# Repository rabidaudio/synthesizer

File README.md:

# Synth

> These are my custom modules for a from-scratch [Eurorack](https://en.wikipedia.org/wiki/Eurorack) analog synthesizer.

https://rabid.audio/projects/synth

## Modules

1. [Amplifier](amp)
  - LM13700
  - matched-pair PNP exponential converter
  - CV of 10V -> Gain=1
  - CV of <=0V -> Gain=\~0, 6 decades below Gain=1
  - allow overdrive to Gain=2
    - ideally this would begin to clip
  - mixdown
    - mono - full mix -> left and right
    - stereo split - A+C->left B+D->right
  - Direct stereo input jack
    - mix arbitrary signal with mixdown
    - e.g. for accepting signals from other synths
2. [Oscillator](vco)
  - 0-10V, 1V/octave, A0 to A10
  - Square/Triangle core via LM13700
  - Waveshapper for triangle -> sine
  - PWM control
    - triangle wave applied to comparator with CV controlling reference. Triangle wave means CV is linear
  - abs(triangle) can be used for 2x square
    - adds a lot of parts for little benefit
  - blending shapes isn't useful here, since we could use other oscillators for that
  - Option to sync with another osc?
    - in theory, grounding osc at a regular interval would reset the osc over and over, effectively changing it's frequency
  - CV control for shape?
  - Room for more shapes
    - white noise?
    - PDS
      - https://en.wikipedia.org/wiki/Phase_distortion_synthesis
      - a bit of wild harmonics
      - multiplication techniques
        - log/antilog
        - https://en.wikipedia.org/wiki/Gilbert_cell
        - AD633 ($11-$13 /unit on DigiKey!?)
        - EL4450C ($4/unit on Digikey but out of stock). It's a little more awkward to use since it's max differerential input voltage for linearity is 2V
      - the hard part will be the "slightly higher frequency" bit
        - perhaps instead you have another osc (555?) running at a fixed frequency and clipping the sine
        - square PWM control could also adjust this clip frequency
      - In Max you do PDS by `kink~`-ing a `phasor~` and using that to drive the phase of `cycle~`. Kink is somewhat straightforward to do - use a comparator to adjust the charge current after a threshold. But how you drive a sine wave phase with that I'm not sure
    - down ramp wave with just a JFET
      - up ramp wave probably needs another JFET and an inverter
    - sub octave
      - theory and example circuit: http://www.valvewizard.co.uk/uboat.html
    - octave
      - full wave rectifier
    - multiplying the triangle with a square wave with different phases and pulse-widths gives some neat sounds
    - polynomial
      - The EL4450C datasheet describes using a multiplier ic to create a polynomial of the form (k1 v^2 + v) / k2
      - it sounds like crap on a triangle wave and does nothing for a square wave, but it adds a nice second harmonic to a sine wave
      - from experiments in Max, good values are k1=1.5-2.5, k2=2
      - but at that point, should you just use 2 oscillators?
3. [A/D/S/R envelope](adsr)
  - 4 envelopes required for 4-voice polyphony
  - wired to VCA by default
  - save surface area with 1 set of ADSR controls for a pair of envelopes
  - fully modular means you could borrow one for VCF instead, or send to both VCA and VCF
4. Filter
  -  4P LP(/HP?)
  - Cutoff frequency control has same range as oscillator
    - 0-10V, 1V/octave, A0 to A10
  - filter we designed for class
    - standard vactrols are available on Thonk
  - CV control of cutoff + resonance
  - Default to track cutoff with VCO-CV
  - individual filter knobs, plus a global knob for filter sweeps
5. [Utilities](utils)
  - Buffer, Sum, Attenuate, Invert, Gate
  - Could be all-in one
    - A input (default ground)
    - B input (default ground)
    - level knob attenuator
    - gate digital CV in, default on
    - `(A+B)*level*gate` output
    - `-(A+B)*level*gate` output
    - Constant CV out if A and B disconnected

Bitcrusher?
4 filters or one?
Noise?
Clock?
Headphone output no longer required
2D mixer?

## TODO

- utility module
  - [x] Verify on breadboard
  - [x] design PCB
  - [x] order parts
  - [x] come up with a cute name
  - [x] design front panel
  - [x] assemble Rev. A PCB
    - bend the regulators first
    - plenty of 4066s
    - flip orientation of power connector
    - pot orientation - both channels:
      - right side (facing) to inside of board (from top)
      - left side (facing) to outside of board (from top)
  - [x] test with Neutron
    - constant output is only 9 to -7.8
    - high noise when used as a buffer
      - perhaps input signal is clipping?
      - white noise when the gain is turned down
  - [x] adjust design for Rev. B
  - [x] assemble Rev. B proto board
  - fix prototype issues
    - [ ] sum pot is backwards
    - [ ] a bit of noise on the constant output near the center
    - [ ] verify output levels
    - [ ] hard click on gate
      - needs a LPF?
  - [ ] assemble Rev. B PCB
  - [ ] manufacture front panel
  - [ ] assemble module
- VCA
  - [x] Confirm amp on breadboard, finalize CV levels
  - [x] figure out where tuning trimmers are needed
  - [x] build prototype
  - fix prototype issues
    - [ ] output is too quiet for headphones, need about 2x gain
    - [ ] CV range is too wide, adjust scaling for faster change in db/V
  - [ ] finish PCB schematic for complete amplifier
  - [ ] Create PCB
  - [ ] design front panel
  - [ ] manufacture front panel
  - [ ] assemble module
- VCO
  - [ ] design core
    - [x] core osc - square/triangle
    - [x] wave shaper (sine)
    - [x] pwm control
    - [ ] additional shape
    - [x] shape selection
  - [x] Confirm amp on breadboard, finalize CV levels
  - fix breadboard test issues
    - [ ] pitch is very sensitive to power supply noise
    - [ ] tuning is rather difficult
  - [ ] Build prototype
  - fix prototype issues
    - TBD
  - [ ] design PCB
  - [ ] Create PCB
  - [ ] design front panel
  - [ ] manufacture front panel
  - [ ] assemble module
- Envelope
  - [x] design in SPICE
  - [ ] verify on breadboard
  - [ ] build prototype
  - fix prototype issues
    - TBD
  - [ ] design PCB
  - [ ] Create PCB
  - [ ] design front panel
  - [ ] manufacture front panel
  - [ ] assemble module
- VCF
  - TBD
- build tools
  - [x] tiny Breakout pcbs for headphone jacks
  - ~~transistor matcher circuit~~
    - bought matched pair BJTs instead
  - [x] quantized selector with hysteresis

## License

Schematics, board layouts, documentation, etc. is licensed under [Creative Commons Attribution-NonCommercial-ShareAlike 4.0 International License](http://creativecommons.org/licenses/by-nc-sa/4.0/).

If you're interested in commercial use, please ask first.

Any source code is licensed under [MIT](SOFTWARE_LICENSE).

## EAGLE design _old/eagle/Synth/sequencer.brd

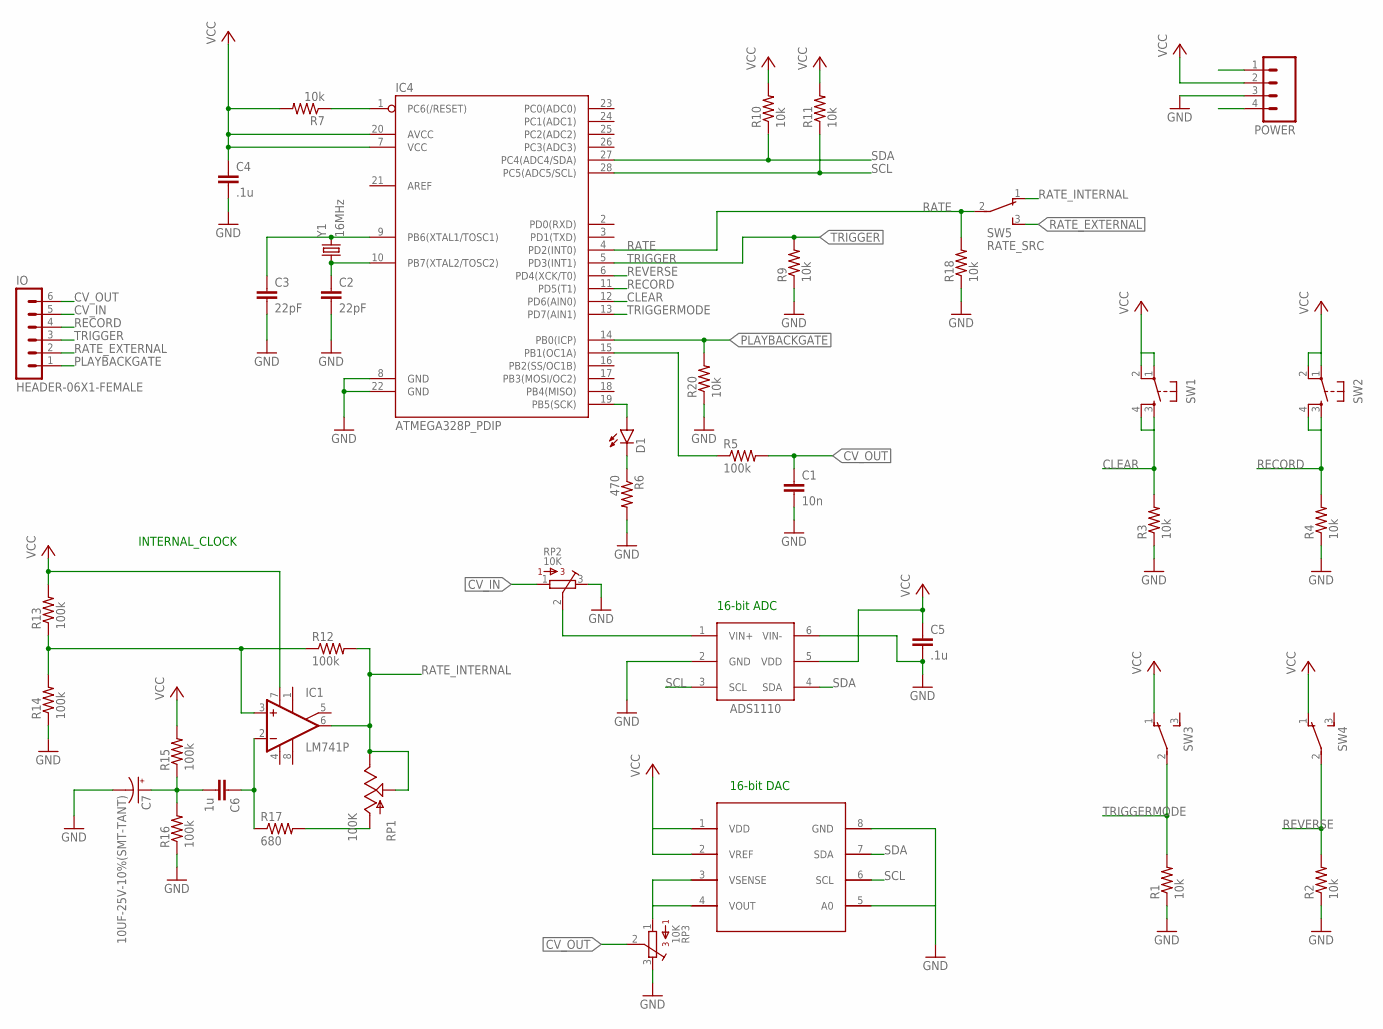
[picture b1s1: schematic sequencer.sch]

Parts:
C1: 10n; 1206
C2, C3: 22pF; 1206
C4, C5: .1u; 1206
C6: 1u; 1206
C7: 10UF-25V-10%(SMT-TANT); EIA6032-NOM
D1: LED-3MM-NO_SILK; LED3MM-NS
IC1: LM741P; DIL08
IC2: ADS1110; SOT-23-6
IC3: DAC8571; 8MSOP
IC4: ATMEGA328P_PDIP; DIL28-3
IO: HEADER-06X1-FEMALE; 06X1-PTH
POWER: M04PTH; 1X04
R1, R2, R3, R4, R7, R9, R10, R11, R18, R20: 10k; 1206
R5, R12, R13, R14, R15, R16: 100k; 1206
R6: 470; 1206
R17: 680; 1206
RP1: 100K; ALPS_POT_KIT
RP2, RP3: 10K; 3386P
SW1, SW2: TAC_SWITCHPTH; TACTILE-PTH
SW3, SW4: TL36YO; TL3XYO
SW5: RATE_SRC; TL3XYO
Y1: 16MHz; HC49US

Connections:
CLEAR: IC4.12 (PD6(AIN0)), R3.2, SW1.3, SW1.4
CV_IN: IO.5, RP2.1
CV_OUT: C1.1, IO.6, R5.2, RP3.2
DIRECT_IN: IC2.1 (VIN+), RP2.2
GND: C1.2, C2.2, C3.2, C4.2, C5.2, C7.C (-), IC2.2 (GND), IC2.6 (VIN-), IC3.5 (A0), IC3.8 (GND), IC4.8 (GND), IC4.22 (GND), POWER.3, R1.1, R2.1, R3.1, R4.1, R6.2, R9.1, R14.1, R16.1, R18.1, R20.1, RP2.3, RP3.3
unnamed: IC4.15 (PB1(OC1A)), R5.1
unnamed: IC3.3 (VSENSE), IC3.4 (VOUT), RP3.1
unnamed: D1.K (C), R6.1
unnamed: IC4.1 (PC6(/RESET)), R7.1
unnamed: C3.1, IC4.9 (PB6(XTAL1/TOSC1)), Y1.2
unnamed: C2.1, IC4.10 (PB7(XTAL2/TOSC2)), Y1.1
unnamed: D1.A, IC4.19 (PB5(SCK))
unnamed: IC1.3 (+IN), R12.1, R13.1, R14.2
unnamed: R17.2, RP1.P$3 (A)
unnamed: C6.2, C7.A (+), R15.1, R16.2
unnamed: C6.1, IC1.2 (-IN), R17.1
PLAYBACKGATE: IC4.14 (PB0(ICP)), IO.1, R20.2
RATE: IC4.4 (PD2(INT0)), R18.2, SW5.2
RATE_EXTERNAL: IO.2, SW5.3 (S)
RATE_INTERNAL: IC1.6 (OUT), R12.2, RP1.P$1 (E), RP1.P$2 (S), SW5.1 (O)
RECORD: IC4.11 (PD5(T1)), IO.4, R4.2, SW2.3, SW2.4
REVERSE: IC4.6 (PD4(XCK/T0)), R2.2, SW4.2
SCL: IC2.3 (SCL), IC3.6 (SCL), IC4.28 (PC5(ADC5/SCL)), R11.1
SDA: IC2.4 (SDA), IC3.7 (SDA), IC4.27 (PC4(ADC4/SDA)), R10.1
TRIGGER: IC4.5 (PD3(INT1)), IO.3, R9.2
TRIGGERMODE: IC4.13 (PD7(AIN1)), R1.2, SW3.2
V-: IC1.4 (V-)
VCC: C4.1, C5.1, IC1.7 (V+), IC2.5 (VDD), IC3.1 (VDD), IC3.2 (VREF), IC4.7 (VCC), IC4.20 (AVCC), POWER.2, R7.2, R10.2, R11.2, R13.2, R15.2, SW1.1, SW1.2, SW2.1, SW2.2, SW3.1 (O), SW4.1 (O)

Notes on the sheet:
INTERNAL_CLOCK
16-bit ADC
16-bit DAC

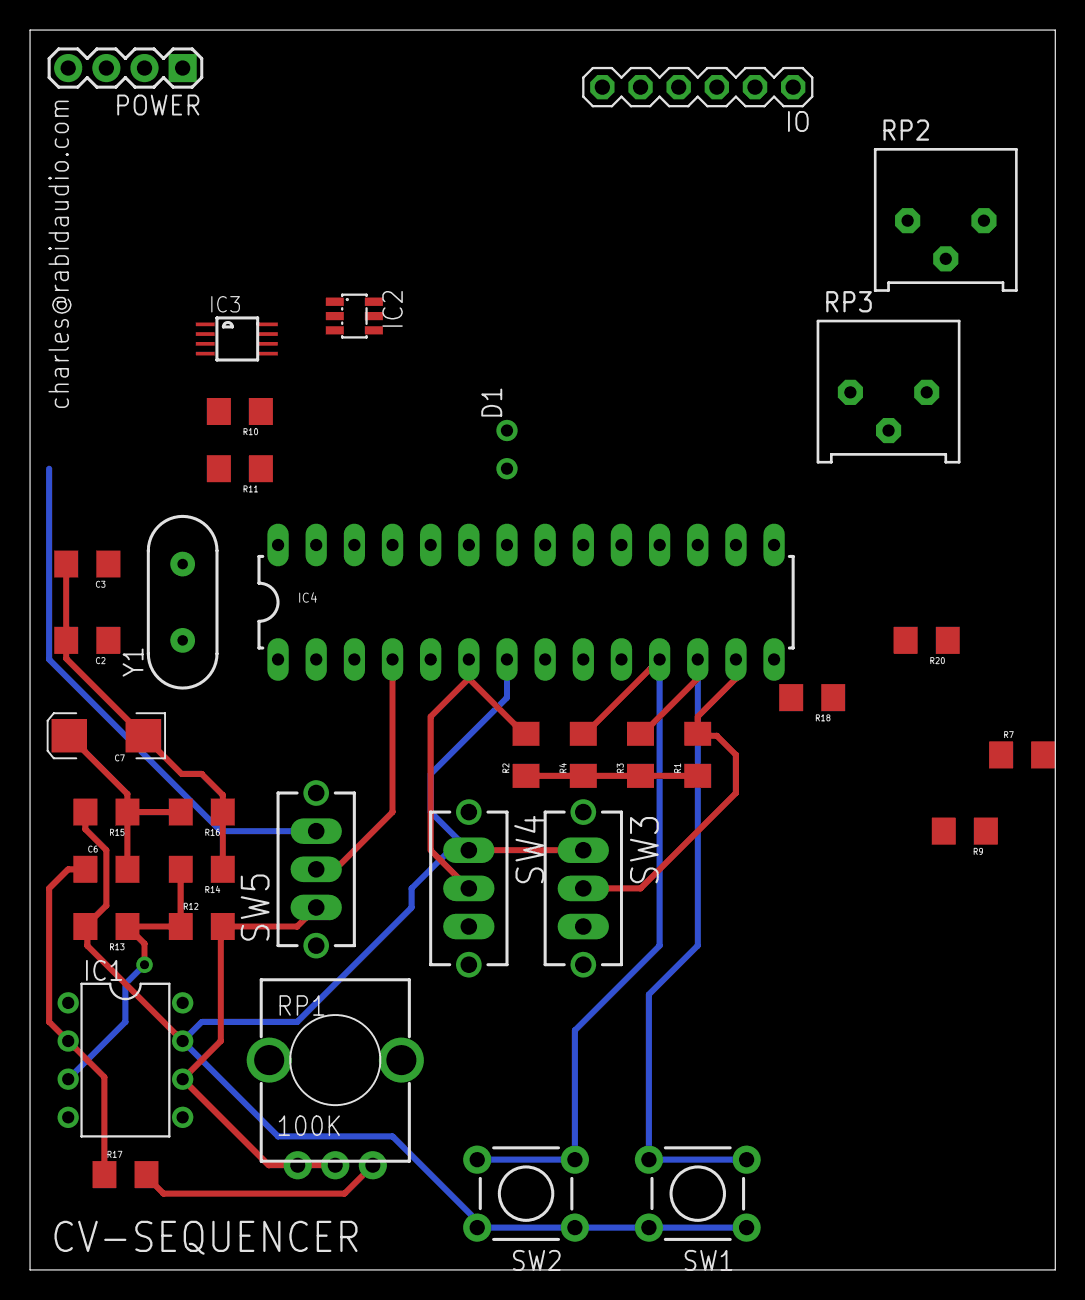
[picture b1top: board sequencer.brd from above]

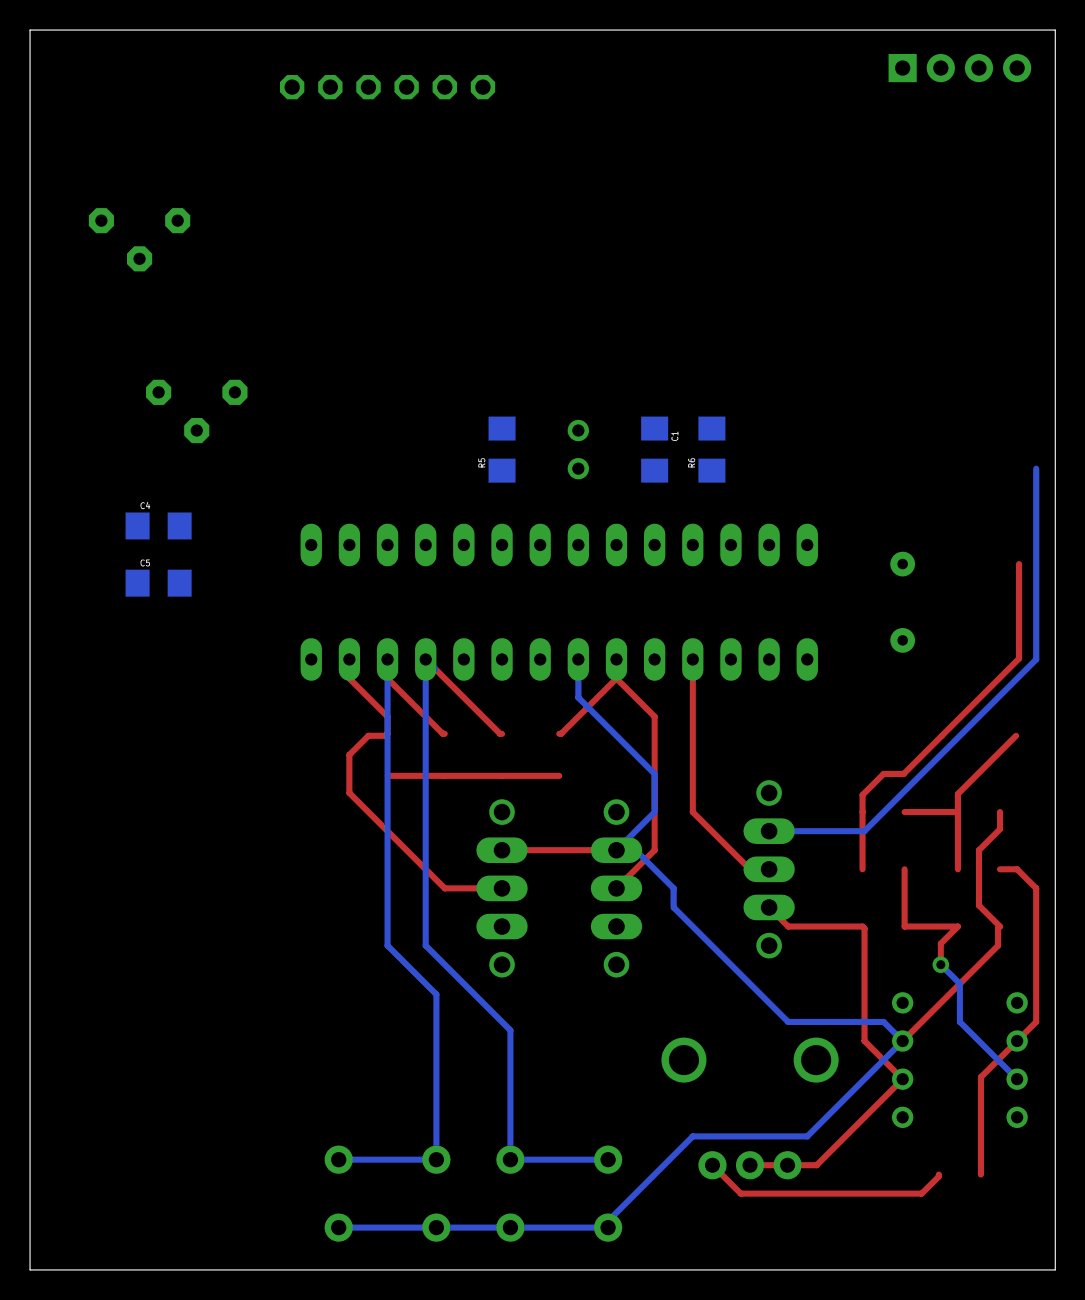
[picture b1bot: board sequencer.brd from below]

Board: 2 copper layers, 68.2 x 82.5 mm, 41 parts (5 on the bottom side), 27 nets.

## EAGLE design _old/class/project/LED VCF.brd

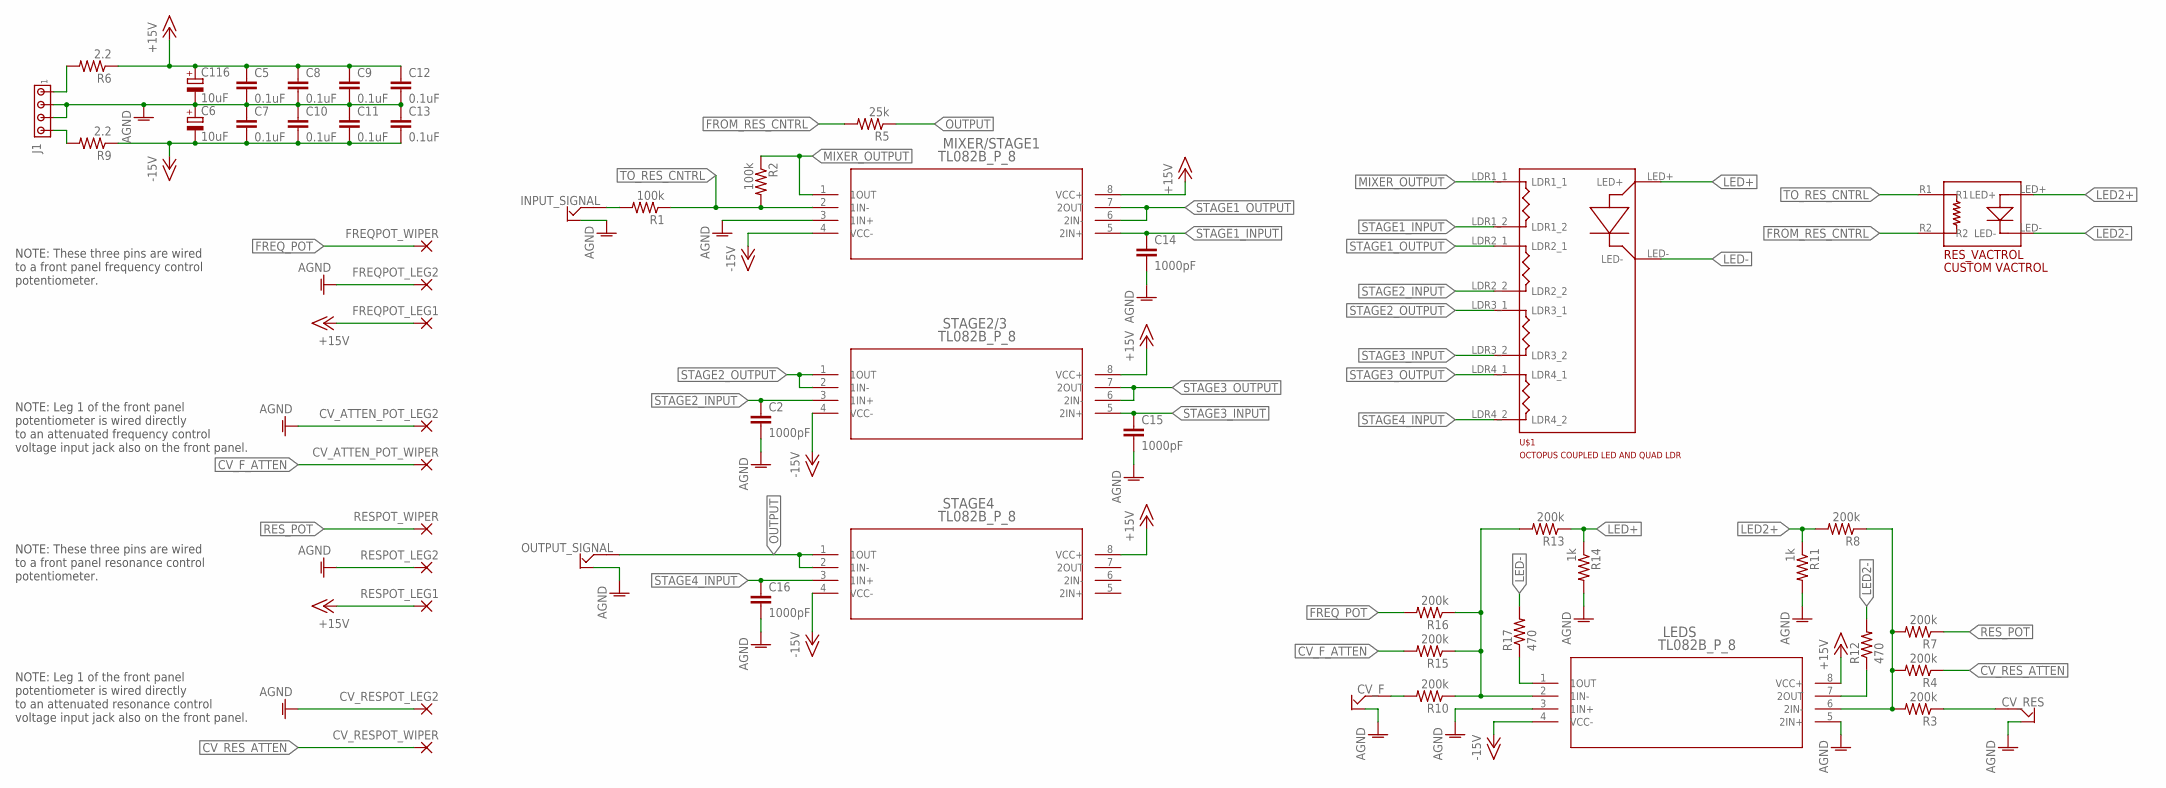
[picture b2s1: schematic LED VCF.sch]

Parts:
C2, C14, C15, C16: 1000pF; AXIAL-5MM
C5, C7, C8, C9, C10, C11, C12, C13: 0.1uF; AXIAL-5MM
C6, C116: 10uF; E1,8-4
CV_ATTEN_POT_LEG2: IOPAD; ELLIPTICALPADSINGLE
CV_ATTEN_POT_WIPER: IOPAD; ELLIPTICALPADSINGLE
CV_F: OFFBOARD2JACK
CV_RES: OFFBOARD2JACK
CV_RESPOT_LEG2: IOPAD; ELLIPTICALPADSINGLE
CV_RESPOT_WIPER: IOPAD; ELLIPTICALPADSINGLE
FREQPOT_LEG1, FREQPOT_LEG2: IOPAD; ELLIPTICALPADSINGLE
FREQPOT_WIPER: IOPAD; ELLIPTICALPADSINGLE
INPUT_SIGNAL: OFFBOARD2JACK
J1: MTA04-156; 1X4MTA
LEDS: TL082B_P_8; P8
MIXER/STAGE1: TL082B_P_8; P8
OUTPUT_SIGNAL: OFFBOARD2JACK
R1, R2: 100k; AXIAL-0.4
R3, R4, R7, R8, R10, R13, R15, R16: 200k; AXIAL-0.4
R5: 25k; AXIAL-0.4
R6, R9: 2.2; AXIAL-0.4
R11, R14: 1k; AXIAL-0.4
R12, R17: 470; AXIAL-0.4
RESPOT_LEG1, RESPOT_LEG2: IOPAD; ELLIPTICALPADSINGLE
RESPOT_WIPER: IOPAD; ELLIPTICALPADSINGLE
RES_VACTROL: CUSTOM_VACTROL_HAYDENTHROUGH-HOLE; CUSTOM_VACTROL_HAYDEN
STAGE2/3, STAGE4: TL082B_P_8; P8
U$1: OCTOPUS_LED_QUAD_LDRTHROUGH_HOLE; OCTOPUS_LED_QUAD_LDR

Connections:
+15V: C5.P$1 (1), C8.P$1 (1), C9.P$1 (1), C12.P$1 (1), C116.+, FREQPOT_LEG1.P$1, LEDS.8 (VCC+), MIXER/STAGE1.8 (VCC+), R6.P$1 (1), RESPOT_LEG1.P$1, STAGE2/3.8 (VCC+), STAGE4.8 (VCC+)
-15V: C6.-, C7.P$2 (2), C10.P$2 (2), C11.P$2 (2), C13.P$2 (2), LEDS.4 (VCC-), MIXER/STAGE1.4 (VCC-), R9.P$1 (1), STAGE2/3.4 (VCC-), STAGE4.4 (VCC-)
AGND: C2.P$2 (2), C5.P$2 (2), C6.+, C7.P$1 (1), C8.P$2 (2), C9.P$2 (2), C10.P$1 (1), C11.P$1 (1), C12.P$2 (2), C13.P$1 (1), C14.P$2 (2), C15.P$2 (2), C16.P$2 (2), C116.-, CV_ATTEN_POT_LEG2.P$1, CV_F.GND, CV_RES.GND, CV_RESPOT_LEG2.P$1, FREQPOT_LEG2.P$1, INPUT_SIGNAL.GND, J1.2, J1.3, LEDS.3 (1IN+), LEDS.5 (2IN+), MIXER/STAGE1.3 (1IN+), OUTPUT_SIGNAL.GND, R11.P$2 (2), R14.P$2 (2), RESPOT_LEG2.P$1
CV_F_ATTEN: CV_ATTEN_POT_WIPER.P$1, R15.P$2 (2)
CV_RES_ATTEN: CV_RESPOT_WIPER.P$1, R4.P$1 (1)
FREQ_POT: FREQPOT_WIPER.P$1, R16.P$2 (2)
FROM_RES_CNTRL: R5.P$2 (2), RES_VACTROL.R2
LED2+: R8.P$2 (2), R11.P$1 (1), RES_VACTROL.LED+
LED2-: R12.P$2 (2), RES_VACTROL.LED-
LED+: R13.P$1 (1), R14.P$1 (1), U$1.LED+
LED-: R17.P$2 (2), U$1.LED-
MIXER_OUTPUT: MIXER/STAGE1.1 (1OUT), R2.P$1 (1), U$1.LDR1_1
unnamed: CV_RES.SIGNAL, R3.P$1 (1)
unnamed: LEDS.6 (2IN-), R3.P$2 (2), R4.P$2 (2), R7.P$2 (2), R8.P$1 (1)
unnamed: J1.1, R6.P$2 (2)
unnamed: INPUT_SIGNAL.SIGNAL, R1.P$2 (2)
unnamed: J1.4, R9.P$2 (2)
unnamed: LEDS.2 (1IN-), R10.P$1 (1), R13.P$2 (2), R15.P$1 (1), R16.P$1 (1)
unnamed: CV_F.SIGNAL, R10.P$2 (2)
unnamed: LEDS.1 (1OUT), R17.P$1 (1)
unnamed: LEDS.7 (2OUT), R12.P$1 (1)
OUTPUT: OUTPUT_SIGNAL.SIGNAL, R5.P$1 (1), STAGE4.1 (1OUT), STAGE4.2 (1IN-)
RES_POT: R7.P$1 (1), RESPOT_WIPER.P$1
STAGE1_INPUT: C14.P$1 (1), MIXER/STAGE1.5 (2IN+), U$1.LDR1_2
STAGE1_OUTPUT: MIXER/STAGE1.6 (2IN-), MIXER/STAGE1.7 (2OUT), U$1.LDR2_1
STAGE2_INPUT: C2.P$1 (1), STAGE2/3.3 (1IN+), U$1.LDR2_2
STAGE2_OUTPUT: STAGE2/3.1 (1OUT), STAGE2/3.2 (1IN-), U$1.LDR3_1
STAGE3_INPUT: C15.P$1 (1), STAGE2/3.5 (2IN+), U$1.LDR3_2
STAGE3_OUTPUT: STAGE2/3.6 (2IN-), STAGE2/3.7 (2OUT), U$1.LDR4_1
STAGE4_INPUT: C16.P$1 (1), STAGE4.3 (1IN+), U$1.LDR4_2
TO_RES_CNTRL: MIXER/STAGE1.2 (1IN-), R1.P$1 (1), R2.P$2 (2), RES_VACTROL.R1

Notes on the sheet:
NOTE: Leg 1 of the front panel potentiometer is wired directly to an attenuated resonance control voltage input jack also on the front panel.
NOTE: These three pins are wired to a front panel frequency control potentiometer.
NOTE: These three pins are wired to a front panel resonance control potentiometer.
NOTE: Leg 1 of the front panel potentiometer is wired directly to an attenuated frequency control voltage input jack also on the front panel.

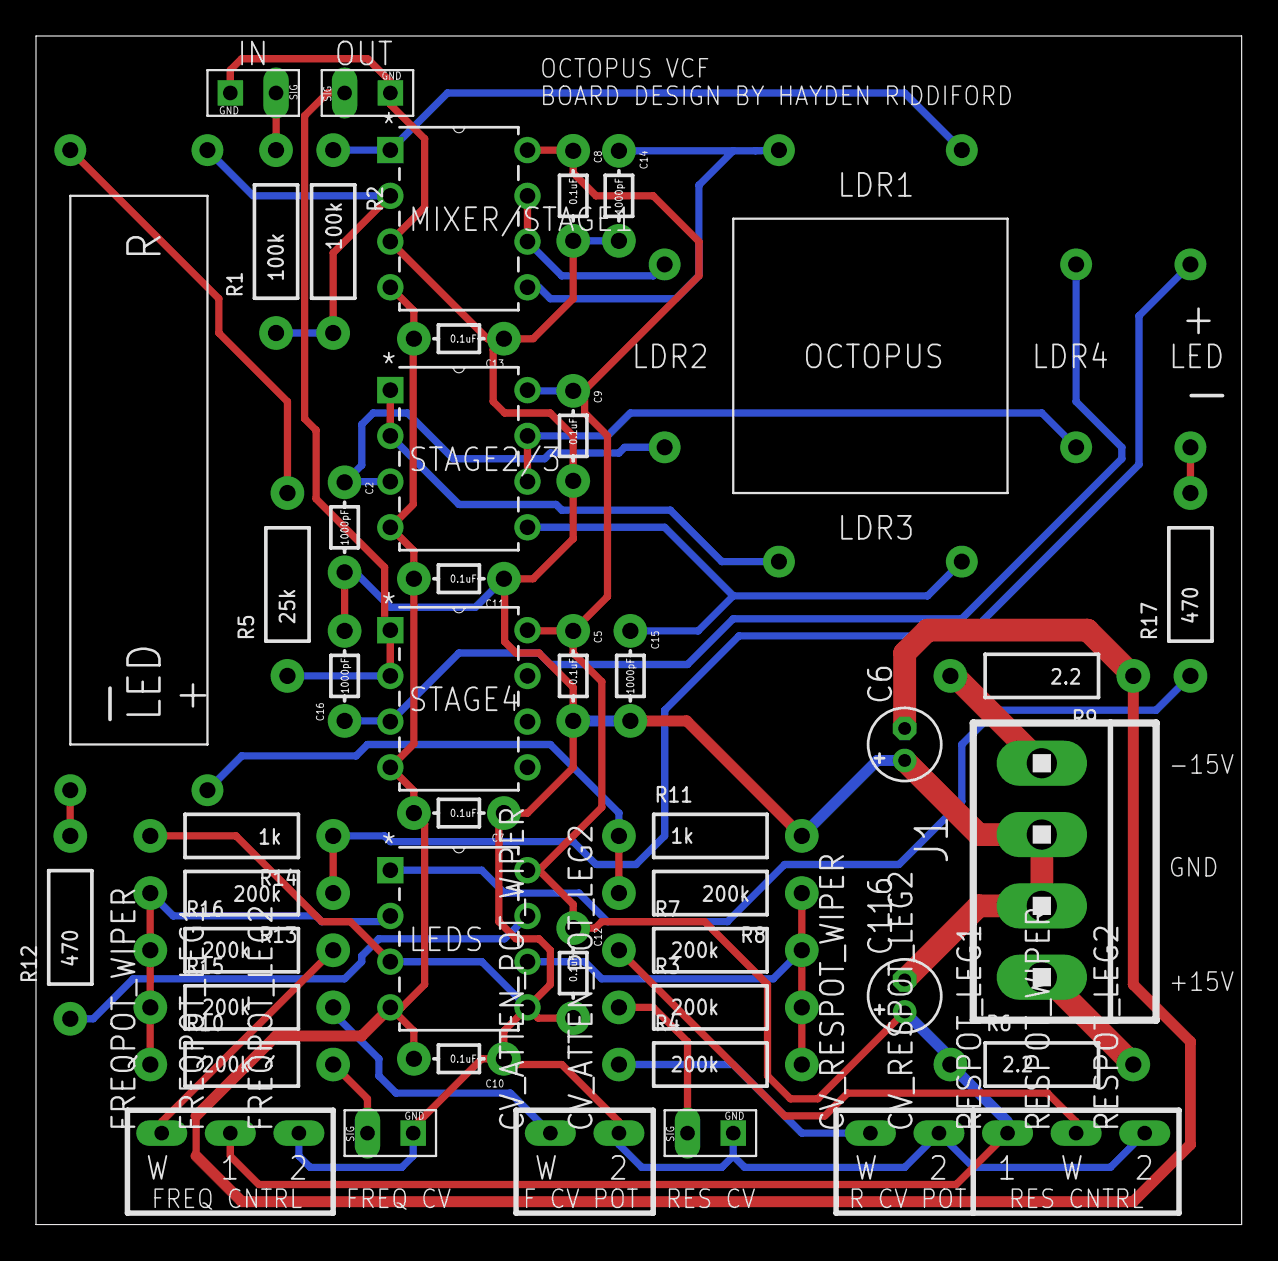
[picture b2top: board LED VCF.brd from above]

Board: 2 copper layers, 67.0 x 66.0 mm, 52 parts (0 on the bottom side), 31 nets.

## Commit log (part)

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2015-04-28 inital commit
2015-05-04 new stuff
2015-05-05 cleaned up
2015-05-05 added classwork
2015-05-05 added textbook
2015-05-05 added ADC, cleaned up schematic
2015-05-05 added osc for seq
2015-05-13 uncommited board changes
2015-05-15 started preso work
2015-05-17 the new sequencer kicks so much ass
2015-05-17 better comments
2015-05-17 updated sequencer eagle files for current version
2015-05-17 updated schematic for BOM
2015-05-20 board tweaks
2015-05-20 added pdf rendering stuff
2015-05-20 basic webcam stuff
2015-05-20 uggh i should have started this hours ago
2015-05-20 uggh
2015-05-20 fuck me
2015-05-20 might just make it
2015-05-20 fuckitshipit
2015-05-20 fingers crossed
2016-07-17 added other files
2019-04-11 started amplifier design
2019-04-15 getting close on the amp
2019-05-28 updated amp - LM13700 with PNP-exp. control
2020-03-15 created base connector breakout project
2020-03-15 10 identical boards
2020-03-15 update amp to kicad 5
2020-03-16 updated amp schematic with glue
2020-03-17 updated VCA based on new calculations
2020-03-17 added notes
2020-03-20 started transistor_matcher circuit
2020-03-20 updated schematic for VBE measurement, started on board layout
2020-03-21 simplfied based on emperical tests
2020-03-28 basic sketch to prove inst. amp is working I think we really need a constant upper reference voltage
2020-03-29 updated to include display
2020-04-05 got working amplifier
2020-04-05 separated amp into sheets
2020-05-03 updated notes
2020-05-20 reworked amp sheets and notes
2020-05-20 update amp config for quad-cascade design
2020-05-20 add eurorack connector, fix some issues
2020-05-21 initial vco notes (not thoroughly validated or calculated
2020-05-21 ltspice sim for lm13700 square/triangle vco
2020-05-23 rename shared kicad dir
2020-05-23 created utility module
2020-05-23 fix for eurorack connector
2020-05-23 added a few more untility footprints
2020-05-24 use jacks directly for horizontal
2020-05-24 switched fet with cd4066
2020-05-24 pcb mostly laid out
2020-05-24 cleanup
2020-05-24 shrunk board
2020-05-24 move the quirks of the pcb out of the schematic
2020-05-24 switch to 10-pin header
2020-05-24 use +/-10V power supply for amps
2020-05-24 reconnect 4066 headers
2020-05-25 LED driver for gate
2020-05-25 experimented some more with the led
2020-05-25 quick prototype of a breadboard power supply connector
2020-05-25 reversed the polarity of the neg cap (oops)
2020-05-28 rework PCB
2020-05-28 shrunk board significantly
2020-05-28 use through-holes for pot
2020-05-30 cleanup repo
2020-05-30 planning pannel layout
2020-05-30 testing 555 as pwm control
2020-05-30 add support for fixed CV output when no input
2020-05-30 correction based on breadboard test
2020-05-31 lots of panel design work
2020-05-31 correct ground issue
2020-05-31 move duplicate directory
2020-06-01 made progress on VCO
2020-06-02 fix some bugs in the circuit
2020-06-02 update graphics based on measurements
2020-06-02 fix amp connector
2020-06-06 it oscilates!
2020-06-06 vco planning
2020-06-06 output selector CV
2020-06-07 started vac layout
2020-06-07 more vca layout
2020-06-08 update amp
2020-06-08 working spice simulation
2020-06-08 added calculations
2020-06-08 adjust params to lower gain=1 current to keep shape up to gain=2
2020-06-08 updated schematic to match
2020-06-08 documented amplifier
2020-06-09 documented utils
2020-06-16 updated vco calculations
2020-06-16 experimenting with error
2020-06-17 add notes from test assembly
2020-07-04 reworked utilities around better analog switch modules
2020-07-04 restarted pcb
2020-07-04 reworked silkscreen
2020-07-04 corrected pin order on the pot breakout
2020-07-05 update components
2020-07-20 started envelope design
2020-07-20 tested utils rev b
2020-08-01 got analog latch working, started schematic
2020-08-01 component selection
2020-08-01 prepared pcb for dual envelopes
2020-08-01 cleanup amp
2020-08-01 clean up documentation
2020-08-01 fix indents
2020-08-02 remove outdated notes
2020-08-02 get rid of propigating controls
2020-08-02 adjusted amp to a 10V control voltage range
2020-08-02 scaled adsr to support 0-10V input
2020-08-02 use a current mirror to isolate reference currents, buffer vin, tune params
2020-08-02 use diode to force positive VIN
2020-08-02 update notes
2020-08-02 more accurate notes about lm13700
2020-08-02 notes
2020-08-03 add max simulation of transfer functions
2020-08-29 corrections based on prototype pcb
2020-08-31 output stage
2020-09-08 vco adjustments
2020-09-12 adjust waveshaper for 12V
2020-09-12 assembled breadboard VCO and waveshaper
2020-09-13 midi poc
2020-12-31 Update README.md
    add note about arp
2021-01-02 unsaved midi changes
2021-01-02 vco notes
2021-01-03 write code for shape selector, design CV input stage of vco
2021-07-07 trying 555 as square wave converter of osc core
2021-09-07 util tweaks
2021-09-11 add vactrol datasheets
2021-09-13 rework ASDR
2021-09-14 more layout
2021-09-14 reduce to one input
2021-09-21 layout
2022-02-06 adsr improvements
2022-09-10 planning and proof-of-concept code
2022-09-10 set up platformio
2022-09-10 refactor code
2022-09-11 switch to attiny84 and think more about control scheme
2022-09-12 add swing support
2022-09-14 basic control mechanism
2022-09-14 improve display
2022-09-14 implement tap tempo
2022-09-15 convert pot to rotary switch
2022-09-15 connect interface to rotary switch
2022-09-19 move reference to blog
2022-09-24 rework clock circuit
2022-09-24 proof-of-concept LED driver
2022-09-24 re-integrate new display with main code
2022-09-25 pcb layout first pass
2022-09-25 cleanup pcb and silkscreen
2022-10-08 additional cleanup
2022-10-08 switch to frequency correct mode and update bpm register values
2022-10-08 CV tempo control
2022-10-08 analog input pin protection
2022-10-16 refactor
2022-10-16 tuned
2022-10-16 reimport backpack code and make def switch for it
2022-10-16 set up code for bare uno option
2022-10-16 get working on bare mcu
2022-10-17 update pcb
2022-10-17 switch side of bottom header for structural support
2022-10-17 simplify some complex routing
2022-11-25 redesign pcb around rotary encoder
2022-11-25 make a bit more space
2023-01-01 testing rotary encoder
2023-01-01 working encoder
2023-01-01 verified hardware
2023-01-01 fix PCB
2023-01-01 beautify schematic
2023-01-02 update to Kicad 6 and fix some layout issues
2023-01-02 update adsr to kicad 6
2023-01-02 re-annotate schematic
2023-01-08 create panel for clock module
2023-01-21 fix 7-segment displays
2023-01-21 fix some PCB bugs
2023-01-21 fix inputs
2023-01-22 pause support
2023-01-31 re-create panel in kicad
2023-02-03 graphics
2023-02-14 updated layout
2023-02-20 updated panel
2023-02-27 new spooky designs
2023-02-27 test out on pcb
2023-03-05 import panel designs and assets
2023-03-05 updated component appearances
2023-03-05 minor adjustments for component bounds
2023-03-05 import alternate design
2023-03-06 make ground plane connected, move LEDs wide
2023-03-06 back graphics
2023-03-07 rendered main design
2023-03-07 added panel to pcb
2023-03-07 render alternate design
2023-03-07 render gerbers
2023-03-18 move logos to soldermask
2023-03-18 fix design issues
2023-03-18 subdivisions both ways
2023-03-18 flip display direction of subdivisions
2023-03-19 add support for saving and loading settings
2023-03-19 display the base value when changing, else true value
2023-03-19 refactor displays to abstract class
2023-04-30 fix swing
2023-04-30 adust resolution of swing to be in %
2023-04-30 rework menu setup
2023-04-30 fix bug in timer
2023-04-30 expand range
2023-04-30 cleanup readme
2023-05-01 increase crystal footprint
2023-05-01 generate rev b gerbers
2023-05-01 cleanup old files
2023-05-01 fixed and separated pcb
2024-10-22 add reusable openscad layout definitions
2024-10-22 create script for extracting center points from openscad dxf
2024-10-23 cleanup synth shared footprints
2024-10-23 flip y orientation
2024-10-23 reverse y-axis orientation
2024-10-23 Revert "reverse y-axis orientation"
    This reverts commit be2b3902423d8e89fe58d89905e9280b5649029d.
2024-10-23 Revert "flip y orientation"
    This reverts commit a8479f8d3d33ab95d629eb13d20a0d69ed88b72e.
2024-10-23 add reverse flag
2024-11-24 keepouts and courtyards for screw components
2024-11-24 fix keepouts
2025-12-01 Bump fonttools from 4.54.1 to 4.61.0 in /shared/extract_dxf_centers
    Bumps [fonttools](https://github.com/fonttools/fonttools) from 4.54.1 to 4.61.0.
    - [Release notes](https://github.com/fonttools/fonttools/releases)
    - [Changelog](https://github.com/fonttools/fonttools/blob/main/NEWS.rst)
    - [Commits](https://github.com/fonttools/fonttools/compare/4.54.1...4.61.0)
    ---
    updated-dependencies:
2025-12-16 Bump filelock from 3.16.1 to 3.20.1 in /shared/extract_dxf_centers
    Bumps [filelock](https://github.com/tox-dev/py-filelock) from 3.16.1 to 3.20.1.
    - [Release notes](https://github.com/tox-dev/py-filelock/releases)
    - [Changelog](https://github.com/tox-dev/filelock/blob/main/docs/changelog.rst)
    - [Commits](https://github.com/tox-dev/py-filelock/compare/3.16.1...3.20.1)
    ---
    updated-dependencies:
2026-01-13 Bump virtualenv from 20.27.0 to 20.36.1 in /shared/extract_dxf_centers
    Bumps [virtualenv](https://github.com/pypa/virtualenv) from 20.27.0 to 20.36.1.
    - [Release notes](https://github.com/pypa/virtualenv/releases)
    - [Changelog](https://github.com/pypa/virtualenv/blob/main/docs/changelog.rst)
    - [Commits](https://github.com/pypa/virtualenv/compare/20.27.0...20.36.1)
    ---
    updated-dependencies:
2026-01-13 Bump filelock from 3.16.1 to 3.20.3 in /shared/extract_dxf_centers
    Bumps [filelock](https://github.com/tox-dev/py-filelock) from 3.16.1 to 3.20.3.
    - [Release notes](https://github.com/tox-dev/py-filelock/releases)
    - [Changelog](https://github.com/tox-dev/filelock/blob/main/docs/changelog.rst)
    - [Commits](https://github.com/tox-dev/py-filelock/compare/3.16.1...3.20.3)
    ---
    updated-dependencies:

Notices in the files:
parts and their libraries:
SparkFun-Passives: Licensing: Creative Commons ShareAlike 4.0 International - https://creativecommons.org/licenses/by-sa/4.0
